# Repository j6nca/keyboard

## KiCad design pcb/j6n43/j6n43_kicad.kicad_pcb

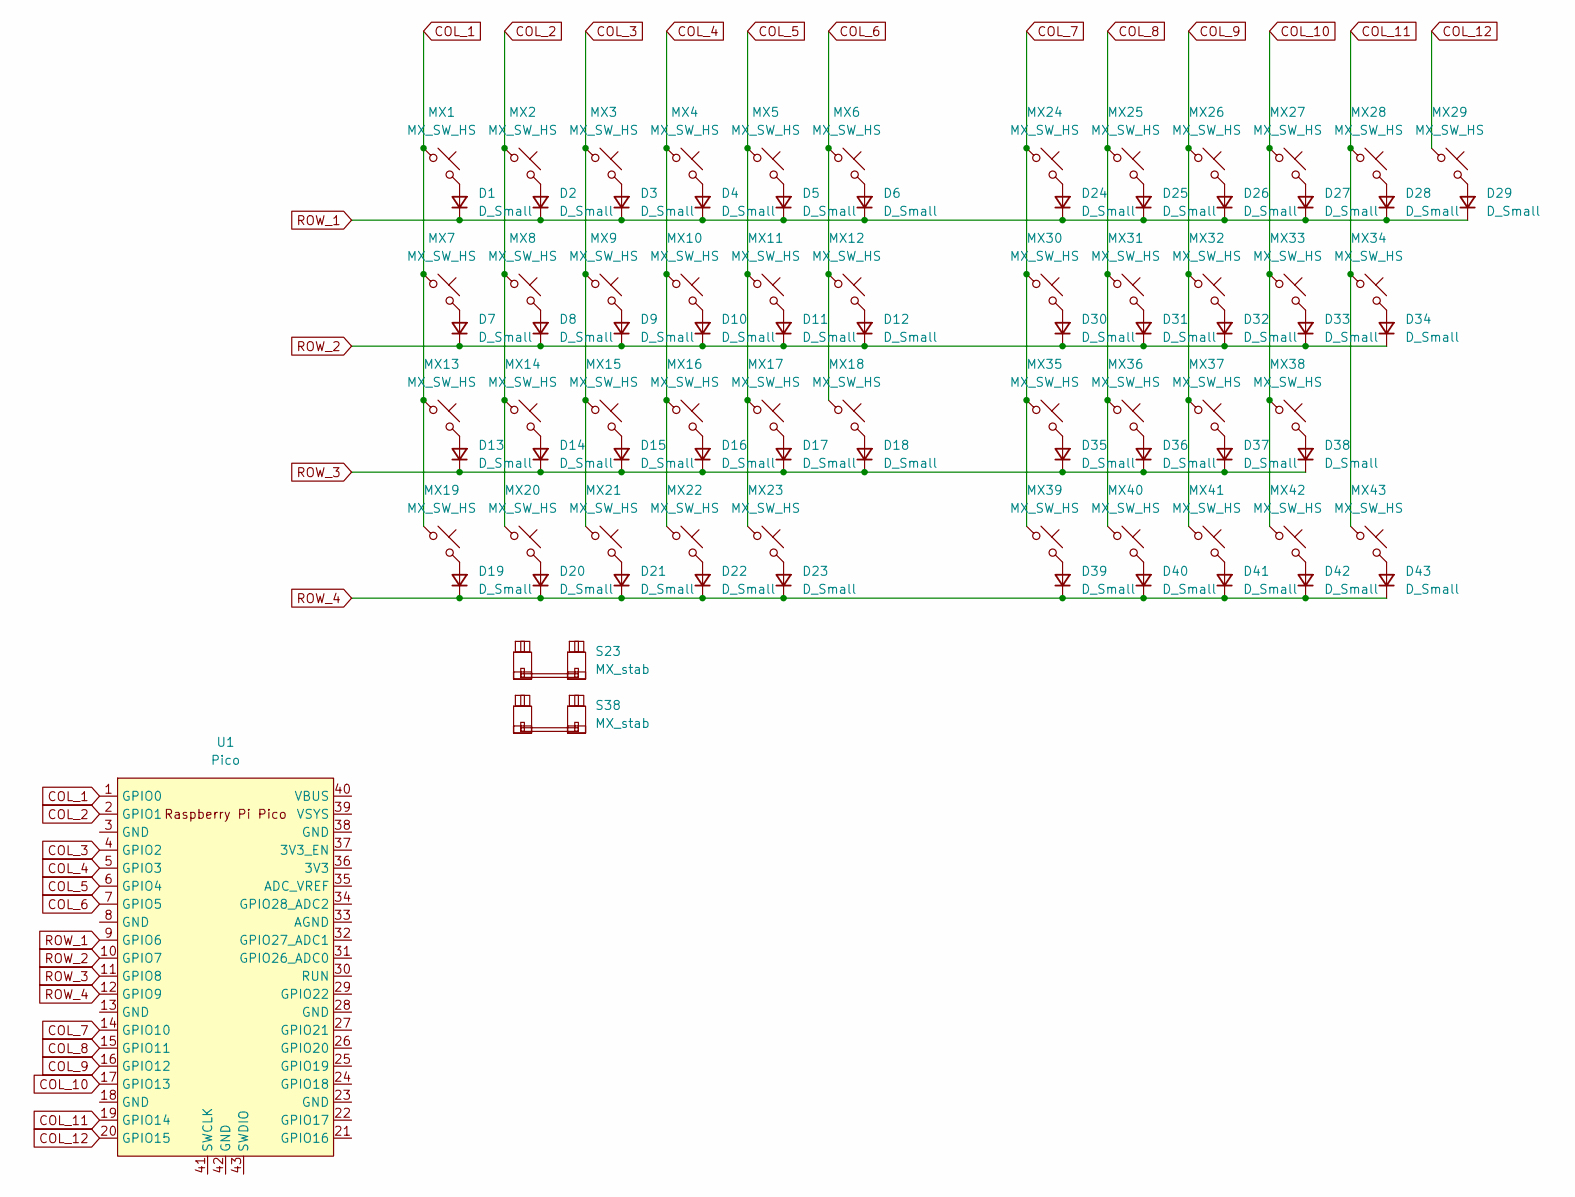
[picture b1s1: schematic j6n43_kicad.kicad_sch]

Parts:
D1, D2, D3, D4, D5, D6, D7, D8, D9, D10, D11, D12, D13, D14, D15, D16, D17, D18, D19, D20, D21, D22, D23, D24, D25, D26, D27, D28, D29, D30, D31, D32, D33, D34, D35, D36, D37, D38, D39, D40, D41, D42, D43: D_Small; D_SOD-123
MX1, MX2, MX3, MX4, MX5, MX6, MX8, MX9, MX10, MX11, MX12, MX13, MX14, MX15, MX16, MX17, MX18, MX20, MX21, MX22, MX23, MX24, MX25, MX26, MX27, MX28, MX29, MX30, MX31, MX32, MX33, MX35, MX36, MX37, MX38, MX40, MX41, MX42, MX43: MX_SW_HS; SW_MX_HS_1u
MX7: MX_SW_HS; SW_MX_HS_1.5u
MX19: MX_SW_HS; SW_MX_HS_1.25u
MX34, MX39: MX_SW_HS; SW_MX_HS_1.75u
S23, S38: MX_stab; STAB_MX_P_2u
U1: Pico; RPi_Pico_SMD_TH

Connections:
COL_1: MX1.1, MX7.1, MX13.1, MX19.1, U1.1 (GPIO0)
COL_2: MX2.1, MX8.1, MX14.1, MX20.1, U1.2 (GPIO1)
COL_3: MX3.1, MX9.1, MX15.1, MX21.1, U1.4 (GPIO2)
COL_4: MX4.1, MX10.1, MX16.1, MX22.1, U1.5 (GPIO3)
COL_5: MX5.1, MX11.1, MX17.1, MX23.1, U1.6 (GPIO4)
COL_6: MX6.1, MX12.1, MX18.1, U1.7 (GPIO5)
COL_7: MX24.1, MX30.1, MX35.1, MX39.1, U1.14 (GPIO10)
COL_8: MX25.1, MX31.1, MX36.1, MX40.1, U1.15 (GPIO11)
COL_9: MX26.1, MX32.1, MX37.1, MX41.1, U1.16 (GPIO12)
COL_10: MX27.1, MX33.1, MX38.1, MX42.1, U1.17 (GPIO13)
COL_11: MX28.1, MX34.1, MX43.1, U1.19 (GPIO14)
COL_12: MX29.1, U1.20 (GPIO15)
unnamed: D1.2 (A), MX1.2
unnamed: D2.2 (A), MX2.2
unnamed: D3.2 (A), MX3.2
unnamed: D4.2 (A), MX4.2
unnamed: D5.2 (A), MX5.2
unnamed: D6.2 (A), MX6.2
unnamed: D7.2 (A), MX7.2
unnamed: D8.2 (A), MX8.2
unnamed: D9.2 (A), MX9.2
unnamed: D10.2 (A), MX10.2
unnamed: D11.2 (A), MX11.2
unnamed: D12.2 (A), MX12.2
unnamed: D13.2 (A), MX13.2
unnamed: D14.2 (A), MX14.2
unnamed: D15.2 (A), MX15.2
unnamed: D16.2 (A), MX16.2
unnamed: D17.2 (A), MX17.2
unnamed: D18.2 (A), MX18.2
unnamed: D19.2 (A), MX19.2
unnamed: D20.2 (A), MX20.2
unnamed: D21.2 (A), MX21.2
unnamed: D22.2 (A), MX22.2
unnamed: D23.2 (A), MX23.2
unnamed: D24.2 (A), MX24.2
unnamed: D25.2 (A), MX25.2
unnamed: D26.2 (A), MX26.2
unnamed: D27.2 (A), MX27.2
unnamed: D28.2 (A), MX28.2
unnamed: D29.2 (A), MX29.2
unnamed: D30.2 (A), MX30.2
unnamed: D31.2 (A), MX31.2
unnamed: D32.2 (A), MX32.2
unnamed: D33.2 (A), MX33.2
unnamed: D34.2 (A), MX34.2
unnamed: D35.2 (A), MX35.2
unnamed: D36.2 (A), MX36.2
unnamed: D37.2 (A), MX37.2
unnamed: D38.2 (A), MX38.2
unnamed: D39.2 (A), MX39.2
unnamed: D40.2 (A), MX40.2
unnamed: D41.2 (A), MX41.2
unnamed: D42.2 (A), MX42.2
unnamed: D43.2 (A), MX43.2
ROW_1: D1.1 (K), D2.1 (K), D3.1 (K), D4.1 (K), D5.1 (K), D6.1 (K), D24.1 (K), D25.1 (K), D26.1 (K), D27.1 (K), D28.1 (K), D29.1 (K), U1.9 (GPIO6)
ROW_2: D7.1 (K), D8.1 (K), D9.1 (K), D10.1 (K), D11.1 (K), D12.1 (K), D30.1 (K), D31.1 (K), D32.1 (K), D33.1 (K), D34.1 (K), U1.10 (GPIO7)
ROW_3: D13.1 (K), D14.1 (K), D15.1 (K), D16.1 (K), D17.1 (K), D18.1 (K), D35.1 (K), D36.1 (K), D37.1 (K), D38.1 (K), U1.11 (GPIO8)
ROW_4: D19.1 (K), D20.1 (K), D21.1 (K), D22.1 (K), D23.1 (K), D39.1 (K), D40.1 (K), D41.1 (K), D42.1 (K), D43.1 (K), U1.12 (GPIO9)

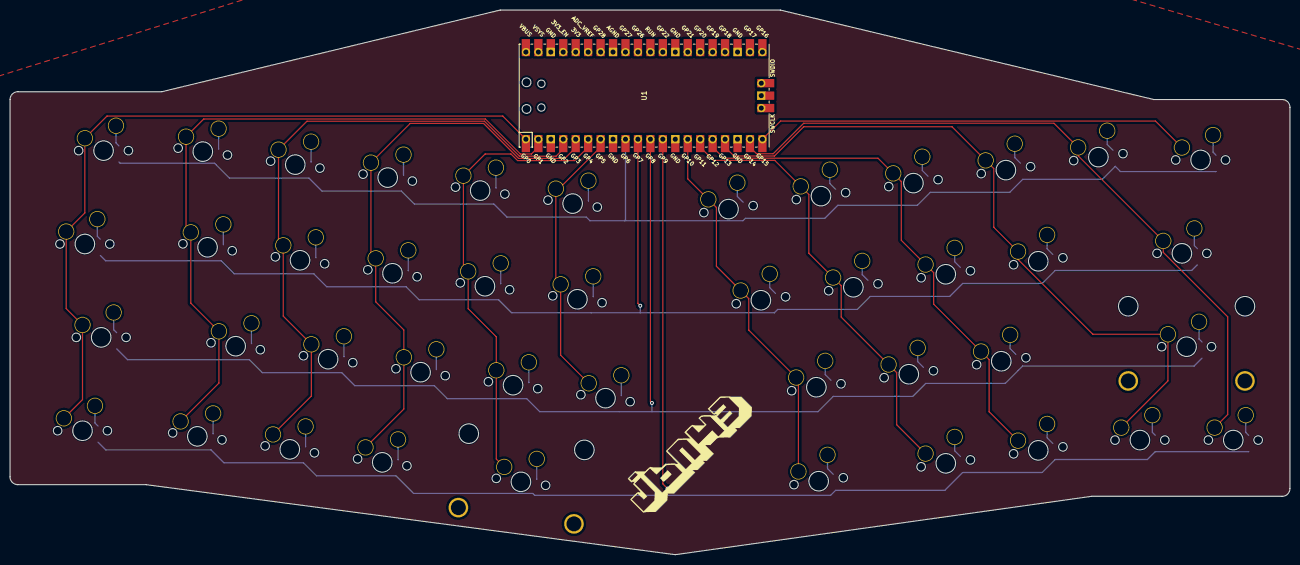
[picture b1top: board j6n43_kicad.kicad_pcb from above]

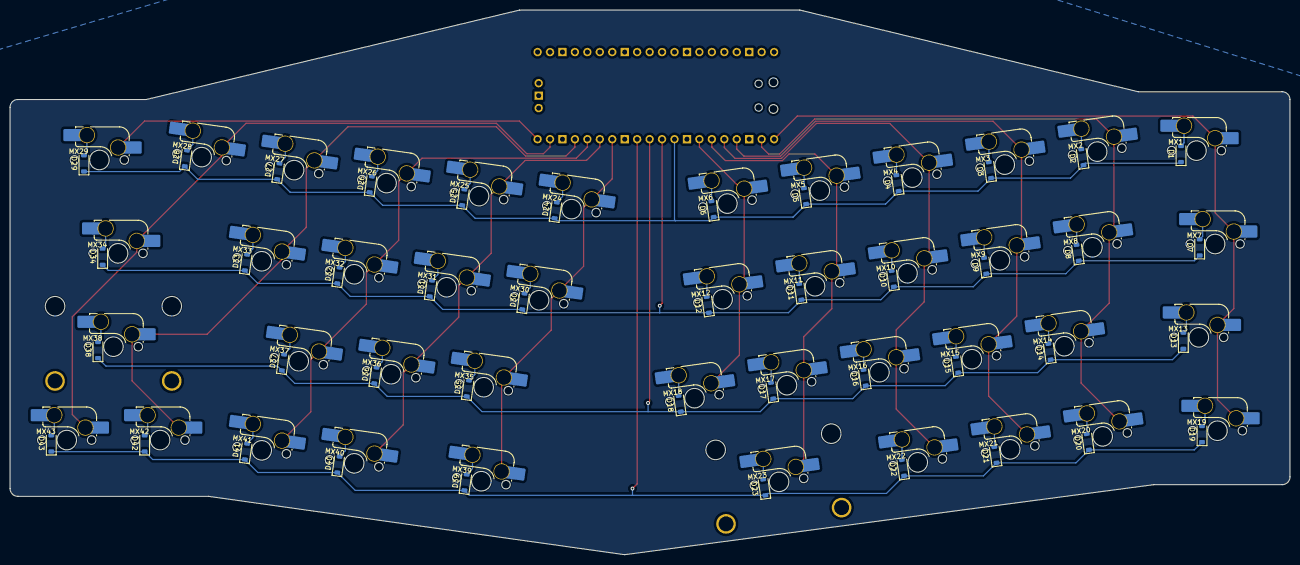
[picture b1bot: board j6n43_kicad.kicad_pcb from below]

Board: 2 copper layers, 261.1 x 111.1 mm, 89 parts (88 on the bottom side), 59 nets.

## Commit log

2023-06-25 adding keychron v4 files
2023-06-26 added some layouts created in kb layout generator
2023-06-26 adding documentation for j6n55
2023-06-26 add diagrams and update docs
2023-06-26 linebreak
2023-06-26 adding references
2023-06-26 update documentation
2023-06-26 add cad file, update docs
2023-06-27 adding j6n58 files
2023-06-27 add cad files for j6n58
2023-06-28 adding new keyboard design
2023-06-28 update costs
2023-07-08 adding via layout configurations
2023-07-25 updated j6n47 docs
2024-05-02 commit old keyboard files
2024-05-02 update custom iris layout
2024-07-23 adding epomaker th40 layout
2024-07-23 update layout, move delete to another layer
